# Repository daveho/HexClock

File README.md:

# HexClock

This is a somewhat silly project to make a digital clock that displays the current time (hour and minute) in hexadecimal.

Here is a picture of the prototype (click to embiggen):

The [KiCad](http://kicad-pcb.org/) schematic for the prototype circuit is in the [hw\_proto](hw_proto) directory.  The required parts are:

* Arduino Nano
* DS1307 i2c real time clock chip
* 4 common anode 7 segment displays
* 4 2N3906 PNP transistors (to switch common anode voltages for LED displays)
* 4 4.7k Ohm resistors (to drive gates of the PNP transistors)
* 2 1K pull-up resistors for i2c SDA and SCL lines
* 7 current limiting resistors for segment cathodes (I used 220 Ohm)
* 3 normally open pushbutton switches
* 5V power supply of some kind

The software is in the [HexClock](HexClock) directory.  It requires the [RTCLib](https://github.com/adafruit/RTClib) and [Bounce2](https://github.com/thomasfredericks/Bounce2) libraries, both of which you can install using the Arduino package manager.

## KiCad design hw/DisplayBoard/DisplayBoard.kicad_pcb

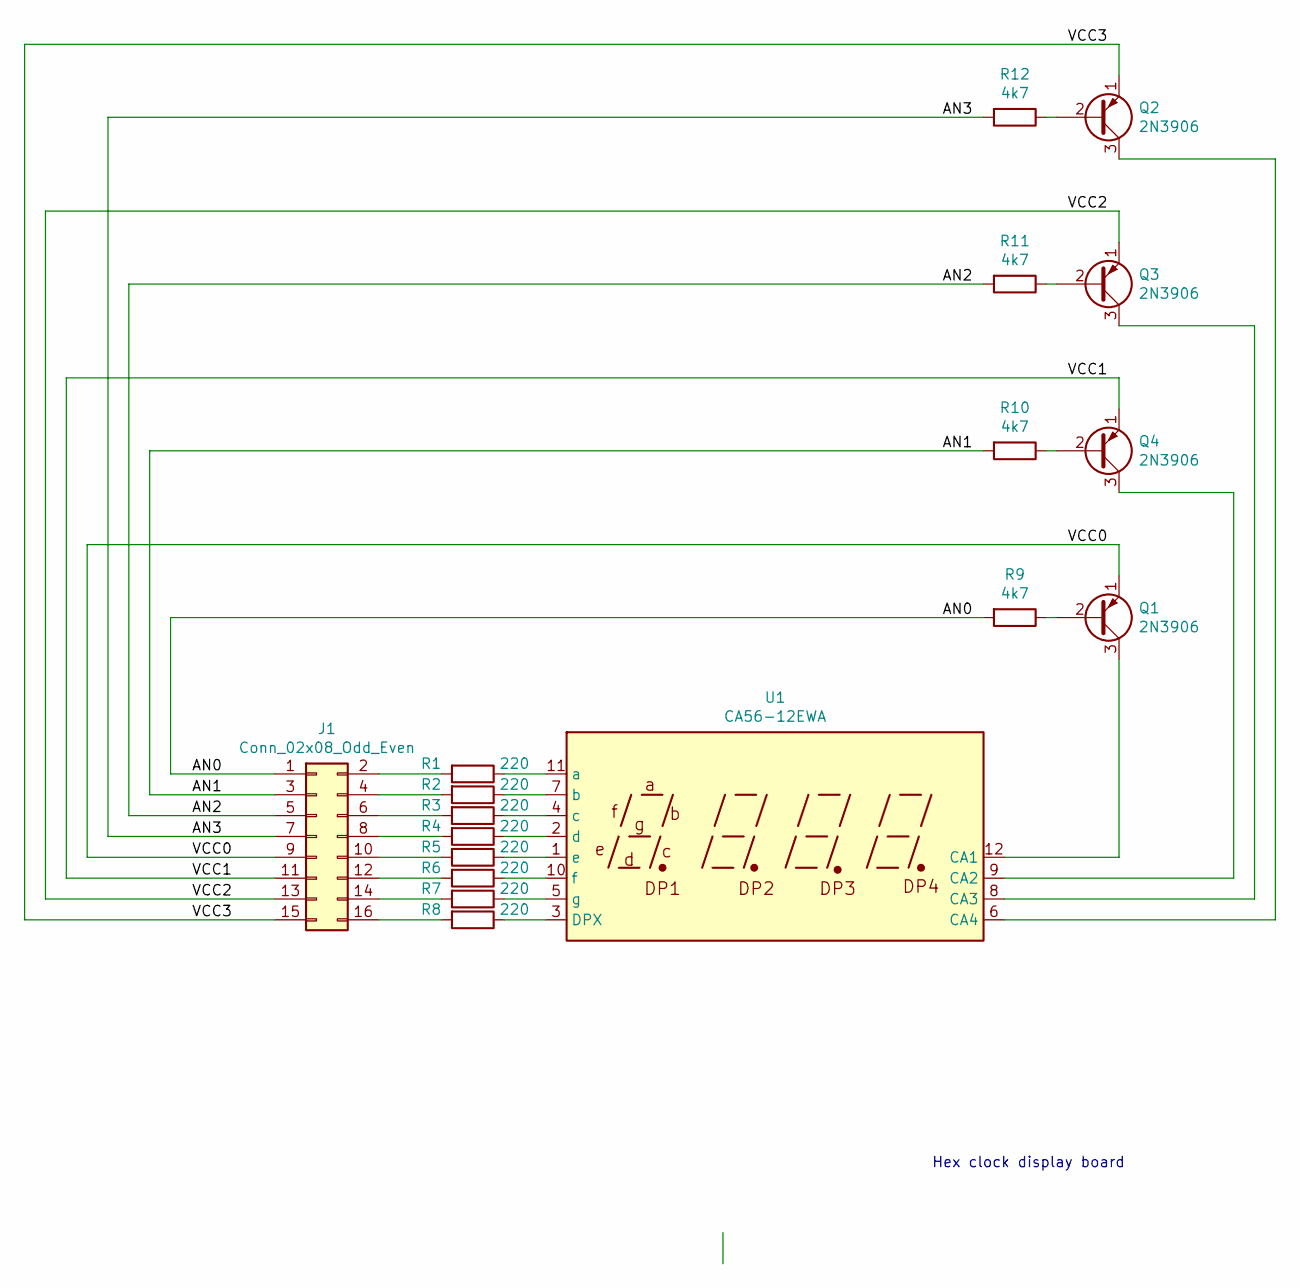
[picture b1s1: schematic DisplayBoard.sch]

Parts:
J1: Conn_02x08_Odd_Even; Pin_Header_Straight_2x08_Pitch2.54mm
Q1, Q2, Q3, Q4: 2N3906; TO-92_Inline_Narrow_Oval
R1, R2, R3, R4, R5, R6, R7, R8: 220; R_Axial_DIN0207_L6.3mm_D2.5mm_P7.62mm_Horizontal
R9, R10, R11, R12: 4k7; R_Axial_DIN0207_L6.3mm_D2.5mm_P7.62mm_Horizontal
U1: CA56-12EWA

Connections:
/AN0: J1.1, R9.2
/AN1: J1.3, R10.2
/AN2: J1.5, R11.2
/AN3: J1.7, R12.2
/VCC0: J1.9, Q1.1 (E)
/VCC1: J1.11, Q4.1 (E)
/VCC2: J1.13, Q3.1 (E)
/VCC3: J1.15, Q2.1 (E)
unnamed: J1.2, R1.2
unnamed: J1.4, R2.2
unnamed: J1.6, R3.2
unnamed: J1.8, R4.2
unnamed: J1.10, R5.2
unnamed: J1.12, R6.2
unnamed: J1.14, R7.2
unnamed: J1.16, R8.2
unnamed: Q1.2 (B), R9.1
unnamed: Q1.3 (C), U1.12 (CA1)
unnamed: Q2.2 (B), R12.1
unnamed: Q2.3 (C), U1.6 (CA4)
unnamed: Q3.2 (B), R11.1
unnamed: Q3.3 (C), U1.8 (CA3)
unnamed: Q4.2 (B), R10.1
unnamed: Q4.3 (C), U1.9 (CA2)
unnamed: R1.1, U1.11 (a)
unnamed: R2.1, U1.7 (b)
unnamed: R3.1, U1.4 (c)
unnamed: R4.1, U1.2 (d)
unnamed: R5.1, U1.1 (e)
unnamed: R6.1, U1.10 (f)
unnamed: R7.1, U1.5 (g)
unnamed: R8.1, U1.3 (DPX)

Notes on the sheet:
Hex clock display board

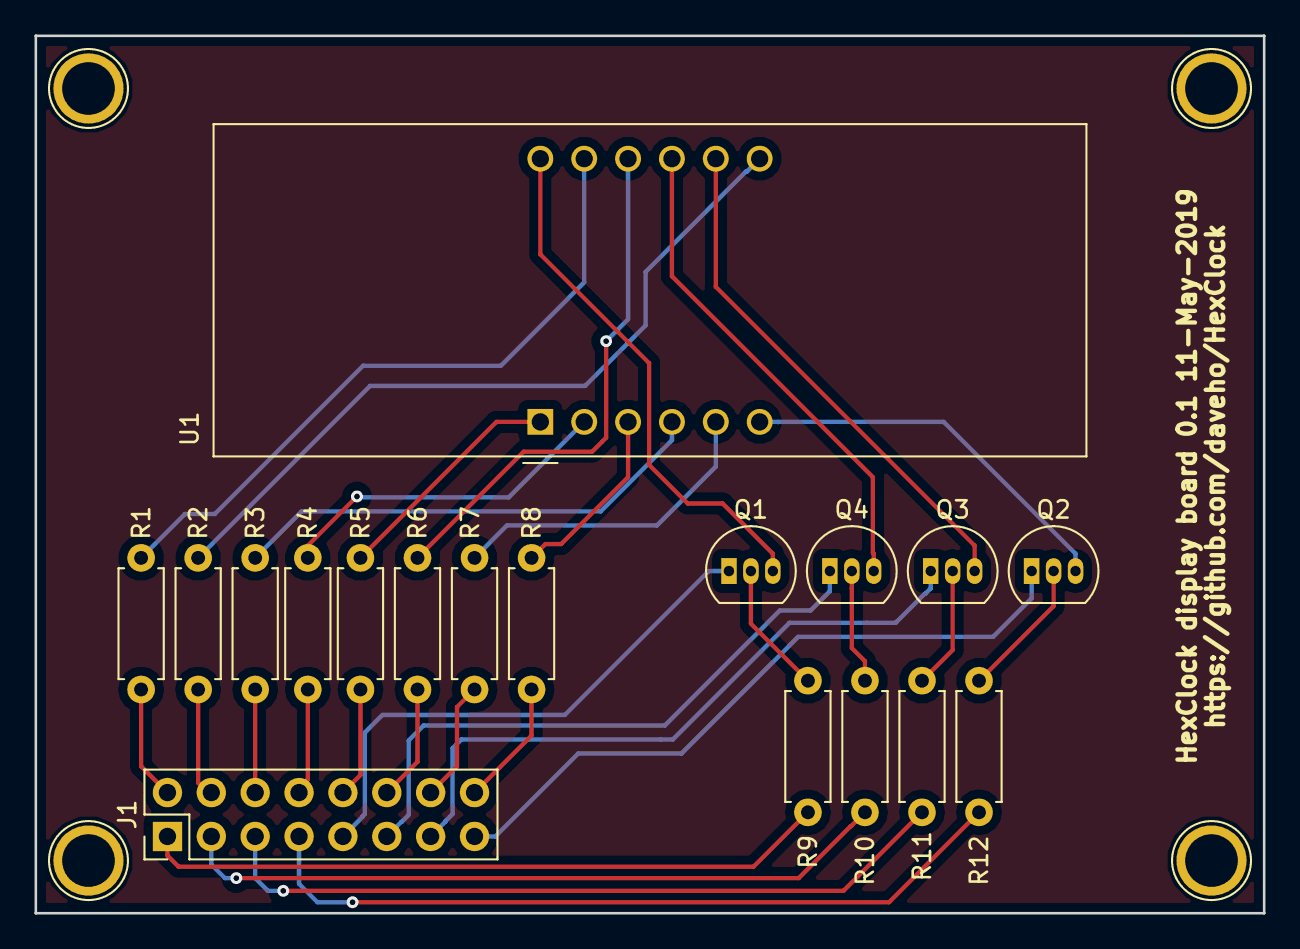
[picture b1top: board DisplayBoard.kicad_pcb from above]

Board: 2 copper layers, 71.1 x 50.8 mm, 18 parts (0 on the bottom side), 32 nets.

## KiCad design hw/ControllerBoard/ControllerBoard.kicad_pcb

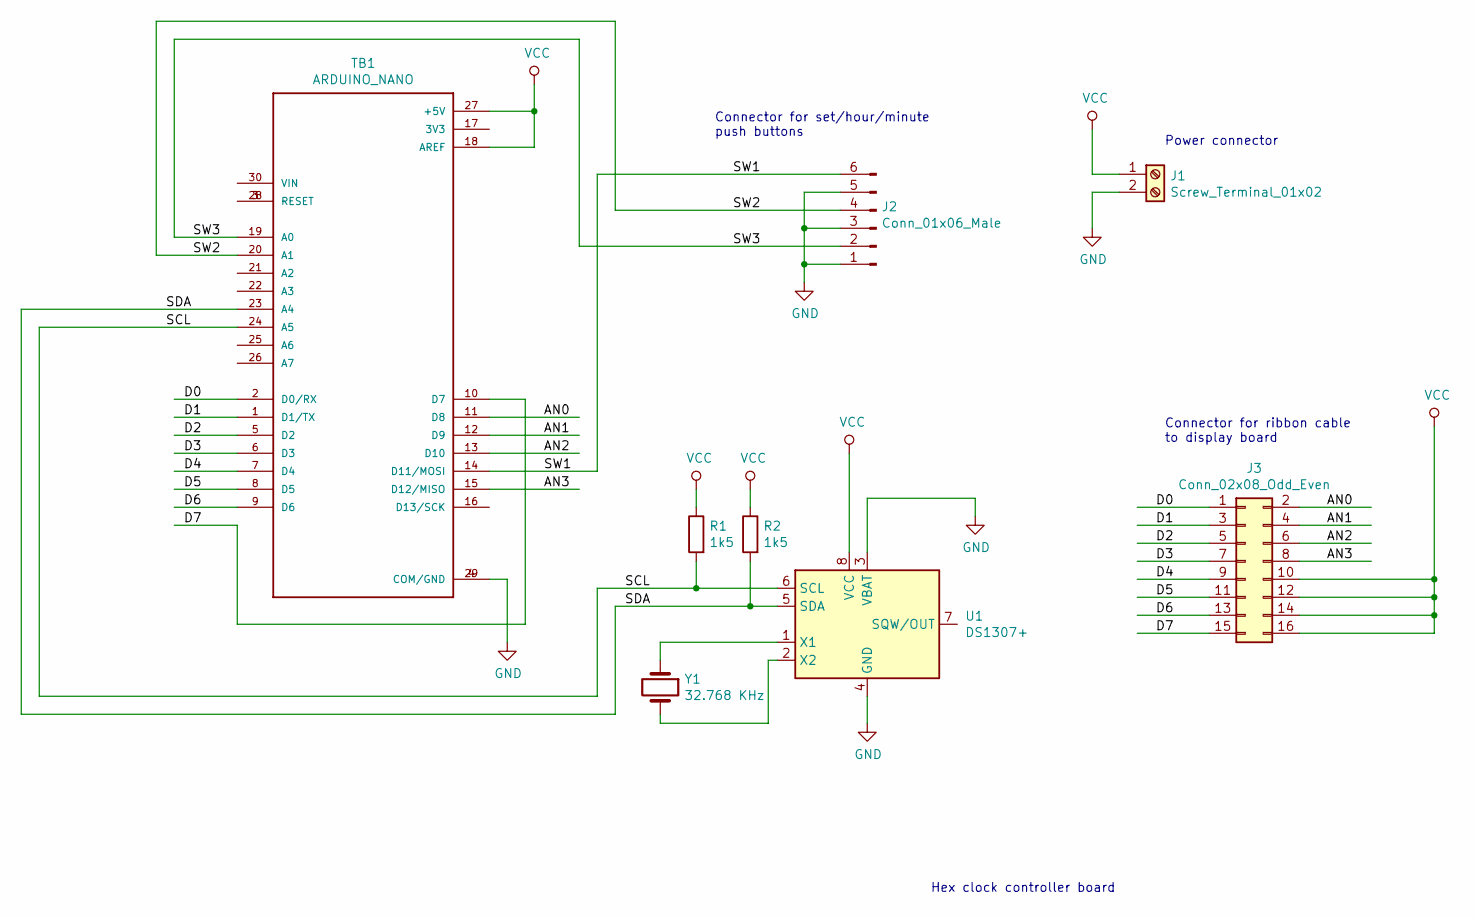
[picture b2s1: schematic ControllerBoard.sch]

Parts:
J1: Screw_Terminal_01x02; TerminalBlock_Phoenix_MKDS-1,5-2_1x02_P5.00mm_Horizontal
J2: Conn_01x06_Male; Pin_Header_Straight_1x06_Pitch2.54mm
J3: Conn_02x08_Odd_Even; Pin_Header_Straight_2x08_Pitch2.54mm
R1, R2: 1k5; R_Axial_DIN0207_L6.3mm_D2.5mm_P7.62mm_Horizontal
TB1: ARDUINO_NANO; SHIELD_ARDUINO_NANO
U1: DS1307+; DIP-8_W7.62mm_Socket
Y1: 32.768 KHz; Crystal_C38-LF_d3.0mm_l8.0mm_Horizontal

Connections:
/AN0: J3.2, TB1.11 (D8)
/AN1: J3.4, TB1.12 (D9)
/AN2: J3.6, TB1.13 (D10)
/AN3: J3.8, TB1.15 (D12/MISO)
/D0: J3.1, TB1.2 (D0/RX)
/D1: J3.3, TB1.1 (D1/TX)
/D2: J3.5, TB1.5 (D2)
/D3: J3.7, TB1.6 (D3)
/D4: J3.9, TB1.7 (D4)
/D5: J3.11, TB1.8 (D5)
/D6: J3.13, TB1.9 (D6)
/D7: J3.15, TB1.10 (D7)
/SCL: R1.2, TB1.24 (A5), U1.6 (SCL)
/SDA: R2.2, TB1.23 (A4), U1.5 (SDA)
/SW1: J2.6, TB1.14 (D11/MOSI)
/SW2: J2.4, TB1.20 (A1)
/SW3: J2.2, TB1.19 (A0)
GND: J1.2, J2.1, J2.3, J2.5, TB1.4 (COM/GND), TB1.29 (COM/GND), U1.3 (VBAT), U1.4 (GND)
unnamed: TB1.3 (RESET), TB1.28 (RESET)
unnamed: U1.1 (X1), Y1.1
unnamed: U1.2 (X2), Y1.2
VCC: J1.1, J3.10, J3.12, J3.14, J3.16, R1.1, R2.1, TB1.18 (AREF), TB1.27 (+5V), U1.8 (VCC)

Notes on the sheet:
Hex clock controller board
Power connector
Connector for set/hour/minute push buttons
Connector for ribbon cable to display board

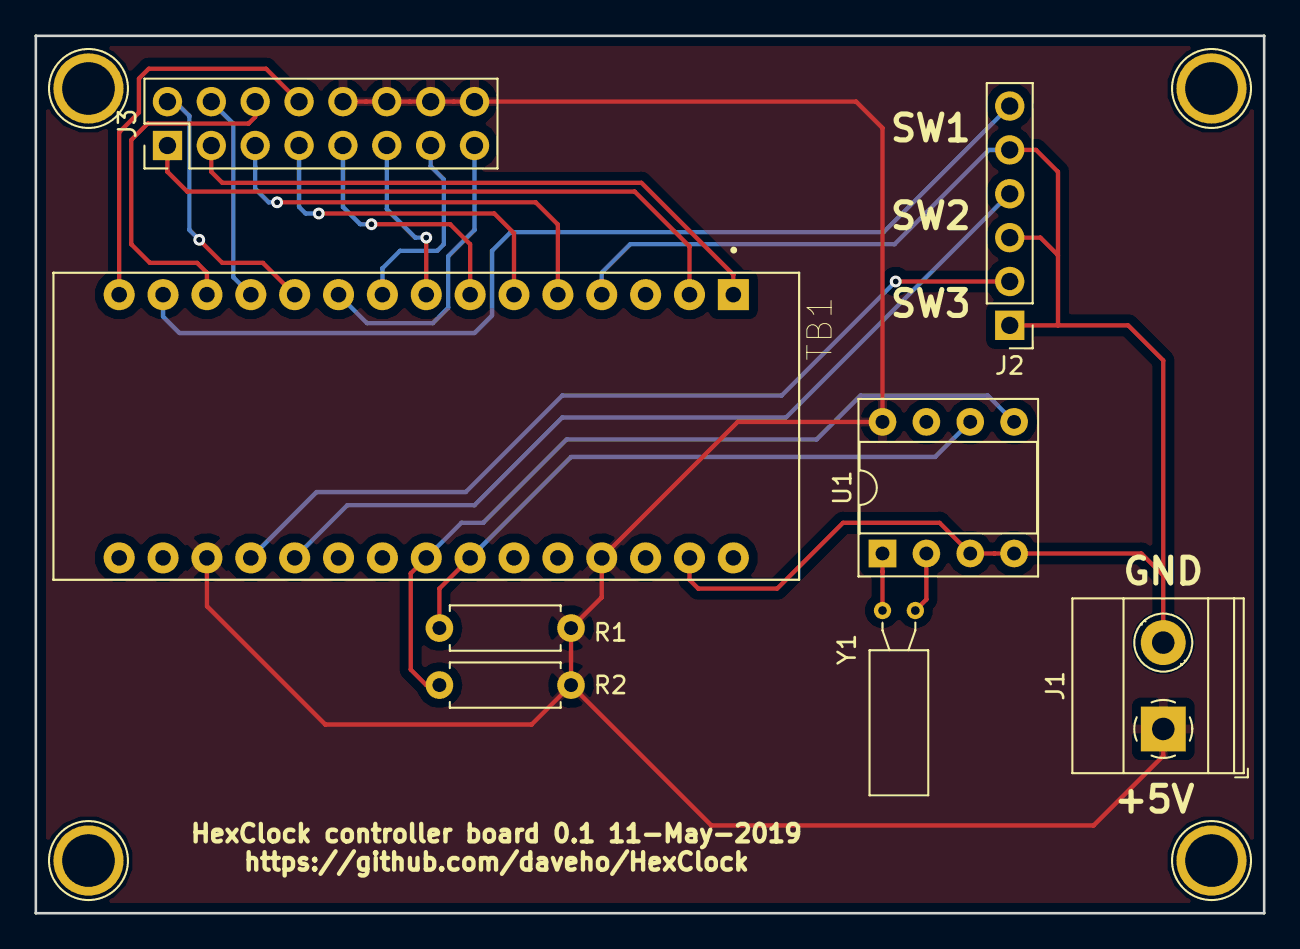
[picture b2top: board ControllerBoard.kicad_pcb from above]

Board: 2 copper layers, 71.1 x 50.8 mm, 8 parts (0 on the bottom side), 22 nets.

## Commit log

2019-04-26 added more code, still not tested
2019-04-26 initial schematic for hardware
2019-04-26 annotated schematic
2019-04-27 use Arduino Nano symbol that has correct pinout
    arduino_nano.lib has the TX and RX pins swapped
2019-04-28 got 7 segment displays working
2019-04-28 less complicated logic to check time
2019-04-30 changed not to use interrupts
2019-04-30 After bugfixes, seems to be working
    Removed the for loop from the loop() function. (Duh.)
    Button 2 is now connected to A1 rather than D13: the
    LED and resistor connected to D13 makes it unsuitable
    as a digital input.
    Still need to clean up the code.
2019-04-30 major code cleanup
2019-04-30 blink decimal point of second display
2019-04-30 further code cleanup
2019-05-01 corrected a code comment
2019-05-01 minor correction to code comment
2019-05-01 added README.md
2019-05-03 added picture of prototype
2019-05-05 set time to midnight on startup
    If the time is not set then the clock doesn't
    seem to run.
    Also, make timing delay a named constant (slowing
    it down is helpful for debugging.)
2019-05-05 power via 5V pin
    Powering via VIN produces strange behavior...
    not sure why.
2019-05-11 tie DS1307 VBAT to ground
    I could not get the DS1307 to work correctly with
    the battery connected.
2019-05-11 moved KiCad project to "hw_proto" directory
    The "production" version of the hardware will
    be two projects, one for the display PCB, one
    for the controller PCB.
2019-05-11 coin cell is no longer used
2019-05-11 start display board project
2019-05-11 edited to make this just the display board
    Also, changed to use a 4 digit LED display.
2019-05-11 generated netlist
2019-05-11 choose component footprints
2019-05-11 reexport netlist with component footprints
2019-05-11 working on PCB layout
2019-05-11 routed all traces
2019-05-11 copper pours on both copper layers
2019-05-11 started controller board project
2019-05-11 updated schematic for controller board
2019-05-11 annotated with component footprints
2019-05-11 fix some footprints, start PCB
2019-05-11 ignore -bak files
2019-05-11 routed all nets, board is ready?
2019-05-11 generated gerber files
2019-05-11 ignore gerber zipfile
2019-05-11 generated (correct?) gerber files
2019-05-26 long press of set button changes display mode
    The decimal display mode isn't actually implemented
    yet.
2019-05-26 implement decimal display mode
